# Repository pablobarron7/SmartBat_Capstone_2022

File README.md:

# SmartBat_Capstone_2022
  The purpose of this project is to allow a Cricket player to get real-time feedback on the user's swing data with out the need of assistance from a coach. The user will be able to view their efficiency, swing speed, and hit location on a user-friendly Android App. 
  
ANDROID APP SUBSYSTEM:
  
  The necessary source files for the android app are located under the "src" folder and include the "build.gradle" and "settings.gradle" files. The Andriod App receives data from our MCU via bluetooth which is then sent to an AWS cloud to be processed by the ML Model. The ML Model will then calcuate the hit location and swing speed. The app will then fetch the calculated results from our AWS Cloud.

CONTROL SUBSYSTEM:
  
  Download the SmartCricketBatOwnCode.ino file, along with the MCU libraries, and use both within Ardunio studio to flash desired ATmega328p microcontroller (make sure  MCU libraries are properly added to Arduino studio's directory after download to avoid any errors). Within the IMU Validation Plots folder are the results from several validation tests performed on the MPU-6050 inertial measurement unit, the plots prove the data recieved from the IMU is accurate, within some margin, to the expected results (raw data text files used to create plots are available within folder as well). 
  
POWER SUBSYSTEM:

  The "FinalPCB" folder contains the EAGLE schematic and PCB board layout files for the project. The PCB contains the battery charging circuit and boost converter circuit  which distribute all the necessary power to the control system. The "powersystemresults" folder contains results for the boost converter load test as well as results for the battery charging circuit.
  
ML SUBSYSTEM:

  All the necessary files are in the ML folder. WIth data collected, "Preprocessing321" to generate features and labels for trainnig the ML. They are named as "feature(1)" and "label(1)". With features and labels, you can traing the model with "Training321" and see the accuracy, heatmap, and feature importance(the seaborn pairplot is comment out). "model1.pkl" is the final model that we use for this project. "sv" is a python file as "sv.py" with stands for server version of my code where it will run on aws EC2 to predict the final results.

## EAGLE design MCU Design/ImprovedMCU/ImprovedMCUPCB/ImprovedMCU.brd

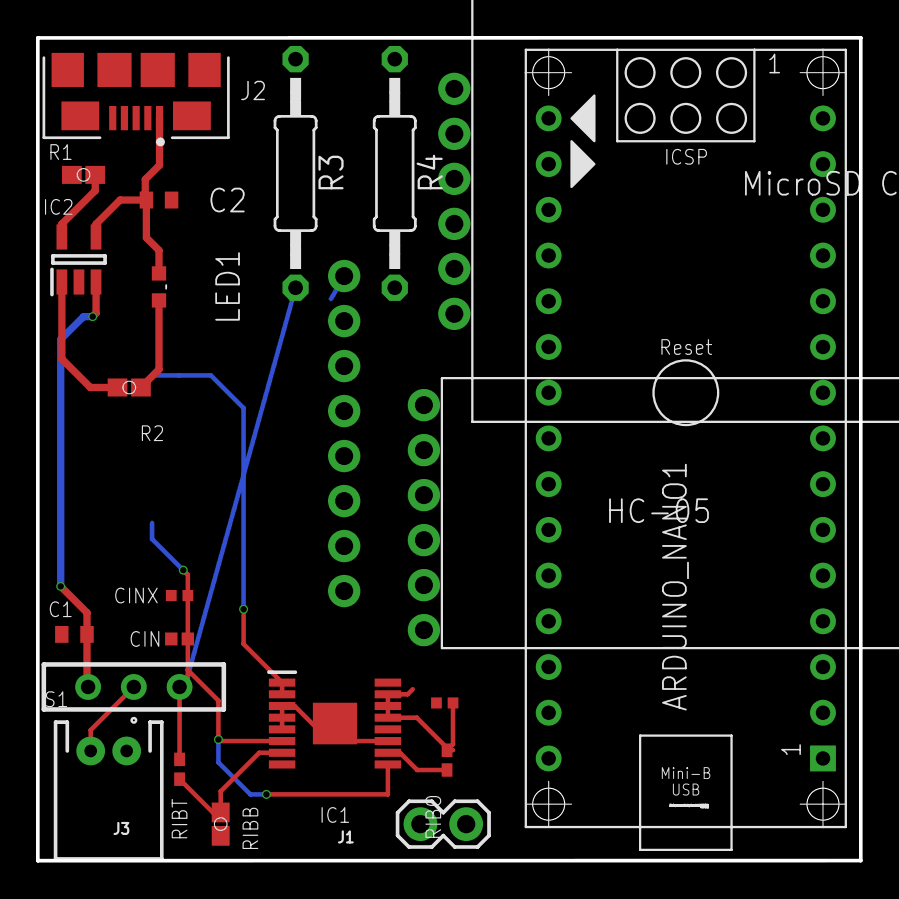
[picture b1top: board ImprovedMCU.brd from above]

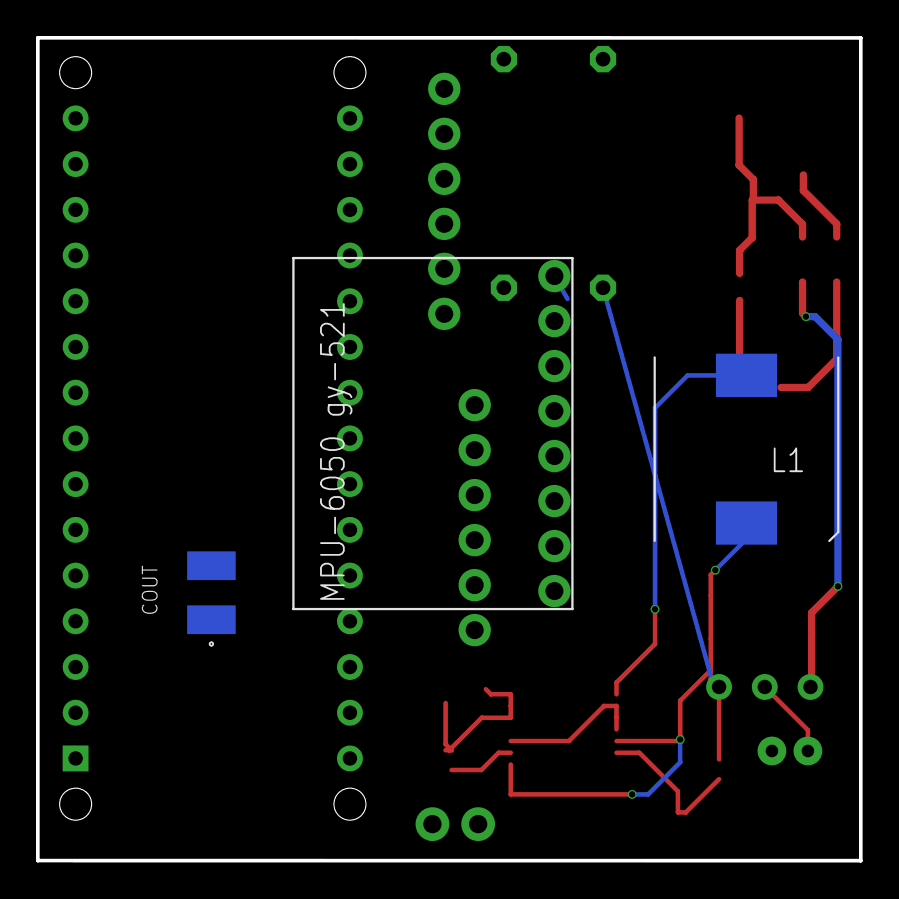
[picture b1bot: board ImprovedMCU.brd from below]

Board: 2 copper layers, 45.7 x 45.7 mm, 25 parts (3 on the bottom side), 12 nets.

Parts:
ARDUINO_NANO1: ARDUINO_NANO
C1, C2: GRM188R6YA475KE15D; CAPC1608X90N
CIN: 10uF; CAPC1005X70N
CINX: 100nF; CAPC1005X55N
COUT: 220uF; POSCAP_B1_B1S_B1G_B15G_B2_B2S
COUTX: 4.7uF; CAPC1005X55N
IC1: TPS61032PWP; SOP65P640X120-17N
IC2: MCP73831T-2ACI_OT; SOT95P270X145-5N
J1: 1X02
J2: AMPHENOL_ICC_-_FCI_10118192-0001LFAMPHENOL_ICC_-_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; AMPHENOL_ICC_-_FCI_10118192-0001LF_0
J3: JST-2-PTH
L1: 3.6uH; WE-PDF59
LED1: VLMS1300-GS08; VLMS1300GS08
R1: RC0603FR-076K65L; RESC1608X55N
R2: RC0603FR-07470RL; RESC1608X55N
R3, R4: 0207/12
RIBB: 390kOhm; RESC1608X55N
RIBO: 1.96MOhm; RESC1005X40N
RIBT: 1.96MOhms; RESC1005X40N
S1: 09.03290.01
U1: GY-521MPU6050; GY-521
U$1: MICROSDMODULE
U$2: HC-05

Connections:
GND: C1.2, C2.2, CIN.1, CINX.1, COUT.2, COUTX.2, IC1.3, IC1.4, IC1.5, IC1.8, IC1.11, IC1.16, IC1.17, IC2.2, J1.2, J2.5, J3.1, R1.2, R4.2, RIBB.1, U1.GND, U$2.GND
unnamed: J3.2, S1.1
unnamed: IC1.10, RIBO.2
unnamed: IC1.7, RIBB.2, RIBT.1
unnamed: LED1.2, R2.1
PROG: IC2.5, R1.1
S$2: COUTX.1, IC1.13, IC1.14, IC1.15, RIBO.1
STAT: IC2.1, R2.2
SW: IC1.1, IC1.2, L1.2
VBAT: CIN.2, CINX.2, IC1.6, IC1.9, L1.1, R3.1, RIBT.2, S1.3
VCHARGE: C1.1, IC2.3, S1.2
VUSB: C2.1, IC2.4, J2.1, LED1.1

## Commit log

2022-11-28 Create ML
2022-11-28 Rename feature(1).txt to ML/feature(1).txt
2022-11-28 Rename label(1).txt to ML/label(1).txt
2022-11-29 Create sv
2022-11-30 ML DATA
    All data collected to train machine learning model
2022-12-01 MCU Design
    Includes improved design with added microSD module for hard copy back-ups and switched microcontroller from Bluno BLE to Arduino Nano
2022-12-01 Bluetooth Validation
    Bluetooth was validated by first walking 10 feet and sending the current distance away from user up until the current distance was not received on the users end (Distance reached ~220-240ft). The Blu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
2022-12-01 ML Validation
    Folder contains individual photos of where the bat physically collided with the bat, the plots output by the machine learning, and the screenshot of the hit location displayed on the phone applicatio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
2022-12-01 Libraries Needed for Final PCB
2022-12-01 Documents
2022-12-03 Demo Videos
    Collection of videos demonstrating how to set-up and use Smart Cricket Bat device.
2022-12-03 Final Documents
    All completed documents
2022-12-03 Update FinalReport_Team22_SmartCricketBat.pdf
    Fixed

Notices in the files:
parts and their libraries:
SparkFun-Connectors: Licensing: Creative Commons ShareAlike 4.0 International - https://creativecommons.org/licenses/by-sa/4.0
